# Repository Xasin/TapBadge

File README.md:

# TapBadge
DIY Smart Home touch badge - control things like in StarTrek!

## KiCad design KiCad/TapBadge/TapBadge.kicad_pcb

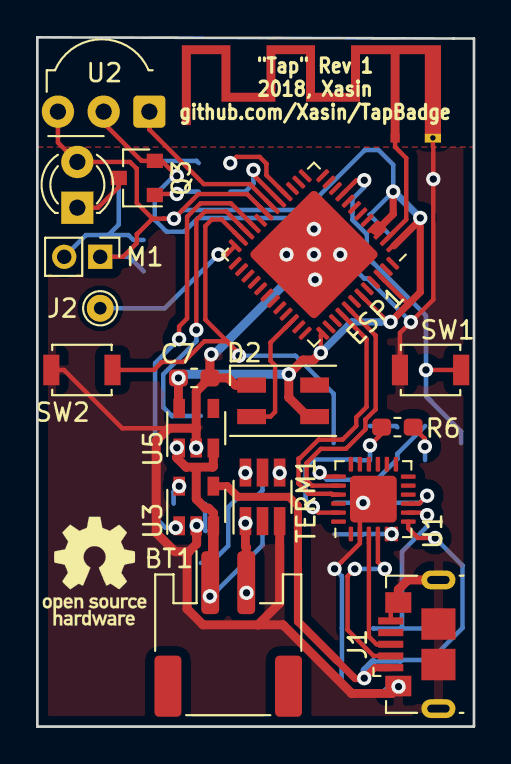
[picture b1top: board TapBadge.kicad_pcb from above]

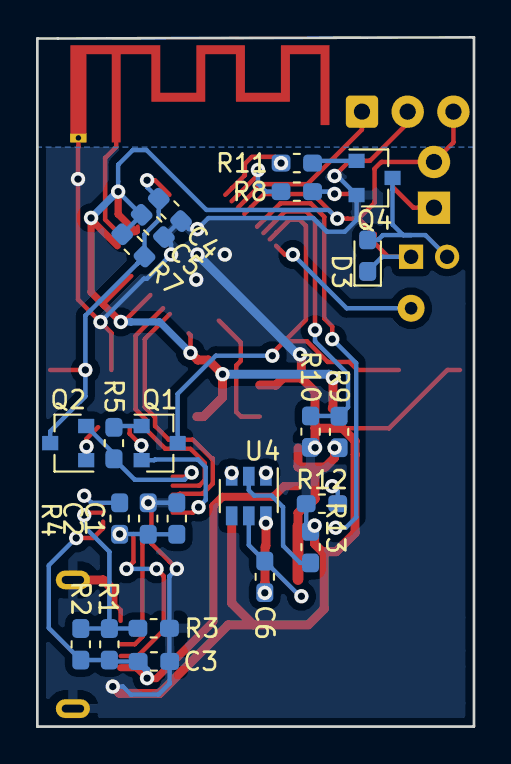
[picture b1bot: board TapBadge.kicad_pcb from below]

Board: 2 copper layers, 24.3 x 38.3 mm, 41 parts (23 on the bottom side), 34 nets.

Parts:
AE1: Antenna_Dipole; Texas_SWRA117D_2.4GHz_Left
BT1: Battery_Cell; JST_PH_S2B-PH-SM4-TB_1x02-1MP_P2.00mm_Horizontal
C1, C3, C7: 10uF; C_0603_1608Metric_Pad1.05x0.95mm_HandSolder
C2, C4, C5, C6: 100nF; C_0603_1608Metric_Pad1.05x0.95mm_HandSolder
D1: SFH4346; LED_D3.0mm_IRBlack
D2: WS2812B; LED_SK6812MINI_PLCC4_3.5x3.5mm_P1.75mm
D3: D_Schottky; D_0603_1608Metric_Pad1.05x0.95mm_HandSolder
ESP1: ESP32PICO_D4; QFN-48-1EP_7x7mm_P0.5mm_EP5.15x5.15mm
J1: USB_B_Mini; USB_Micro-B_GCT_USB3076-30-A
J2: Conn_01x01_Male; TestPoint_THTPad_D1.5mm_Drill0.7mm
M1: Motor_DC_ALT; PinHeader_1x02_P2.00mm_Vertical
Q1, Q2, Q3, Q4: Q_NPN_BEC; SOT-23
R1: R_Small; R_0603_1608Metric_Pad1.05x0.95mm_HandSolder
R2, R3, R5, R6, R7, R11: 10k; R_0603_1608Metric_Pad1.05x0.95mm_HandSolder
R4, R8, R12, R13: 2.2k; R_0603_1608Metric_Pad1.05x0.95mm_HandSolder
R9, R10: 100k; R_0603_1608Metric_Pad1.05x0.95mm_HandSolder
SW1, SW2: SW_Push; SW_SPST_B3U-1000P
TERM1: FS8205; SOT-23-6_Handsoldering
U1: CP2102N-A01-GQFN24; QFN-24-1EP_4x4mm_P0.5mm_EP2.6x2.6mm
U2: TSOP4840; Vishay_MOLD-3Pin
U3: MCP73831-2-OT; SOT-23-5
U4: FS312F-G; SOT-23-6
U5: SPX3819M5-L-3-3; SOT-23-5

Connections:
+3V3: C5.1, C7.1, D1.2, D2.1, D3.1, ESP1.1, ESP1.3, ESP1.4, ESP1.19, ESP1.37, ESP1.43, ESP1.46, M1.1, R7.1, U2.3, U5.5
+5V: C3.2, J1.1, R1.1, R2.1, U1.7, U3.4
+BATT: BT1.1, C6.2, R9.1, U3.3, U4.5, U5.1, U5.3
/ANT: AE1.1, ESP1.2
/CHG_STAT: ESP1.21, U3.1
/E->U: ESP1.41, U1.20
/GPIO0: ESP1.23, Q1.3, SW2.2
/IR_IN: ESP1.18, U2.1
/IR_OUT: ESP1.17, R8.2
/RESET: C4.1, ESP1.9, Q2.3, R7.2, SW1.2
/RGB_IO: D2.4, ESP1.34
/TOUCH0: ESP1.24, J2.1
/U->E: ESP1.40, U1.21
/VBR: ESP1.16, R11.2
GND: AE1.2, C1.2, C2.2, C3.1, C4.2, C5.2, C7.2, D2.3, ESP1.49, J1.5, J1.6, Q3.2, Q4.2, R3.2, R10.2, R12.1, R13.2, SW1.1, SW2.1, TERM1.3, U1.2, U1.25, U2.2, U3.2, U5.2
unnamed: BT1.2, C6.1, TERM1.1, U4.6
unnamed: C1.1, C2.1, R4.1, U1.5, U1.6
unnamed: D1.1, Q3.3
unnamed: D3.2, M1.2, Q4.3
unnamed: ESP1.22, R9.2, R10.1
unnamed: J1.2, U1.4
unnamed: J1.3, U1.3
unnamed: Q1.1, R5.1
unnamed: Q1.2, R6.2, U1.23
unnamed: Q2.1, R6.1
unnamed: Q2.2, R5.2, U1.19
unnamed: Q3.1, R8.1
unnamed: Q4.1, R11.1
unnamed: R1.2, R2.2, R3.1, U1.8
unnamed: R4.2, U1.9
unnamed: R12.2, U3.5
unnamed: R13.1, U4.2
unnamed: TERM1.4, U4.3
unnamed: TERM1.6, U4.1

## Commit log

2018-09-01 ESP32 build env init
2018-09-10 First playing around with ESP
2018-09-10 First rev of the Tap Badge schematic. WIP
2018-09-16 Using C++, added Touch and NeoPixel classes
2018-09-16 Completed rev1 PCB
2018-10-08 Added last few 3D models
2018-10-08 Small timer type change
2018-10-08 Fixed mutex usage
2018-10-08 Updated config for BT
2018-10-08 Added handler for LED output
2018-10-08 First version of a BLE handler class
2018-10-08 Included new BLE class
2018-10-14 BLE Service file added
2018-10-14 BLE Characteristic class added
2018-10-14 Using new classes in handler
2018-10-14 Testing classes
2018-10-14 SDKConfig update
2018-10-17 Got the BLEHandler system into a working state
2018-10-19 Tried fixing bluetooth characteristic update fail
2018-10-20 Removed charge status pin
2018-10-20 Added read and write functions to Characteristic.h
2018-10-20 Playing with stuff
2018-10-23 Added 'return to base color' function
2018-10-23 Small improvements to NeoController
2018-10-23 Added ISR triggering and detect handle notifying
2018-10-23 Rev.1 of the morsecode parser :D
2018-10-23 Trying to power-optimize BLE
2018-10-23 Playing with BLE power
2018-10-23 Added better mode control
2018-10-23 Added 'off' command
2018-10-24 Small mods to Main
2018-10-24 Moved bluedroid init into contstructor
2018-10-24 Stripping project to minimal error production
2018-10-24 Debug work
2018-10-24 Removed encryption
2018-10-24 Added status target for powerdown phase
2018-10-24 Added convenience value setter functions
2018-10-24 Made Services default primary
2018-10-24 Added pre-built components
2018-10-24 Played with new components
2018-10-25 Added power-target for auto-power-down
2018-10-25 Forgot to add main
2018-10-26 Attempt at debouncing
2018-10-31 Fine tuning of values
2018-10-31 Fixed CPU freq to 80MHz
2018-10-31 Fixed adv-stop with no stop time
2018-10-31 First small version of the TapApp
2018-10-31 Added gitignore for the build output
2018-11-05 Added client connection timestamp and fixed data send
2018-11-05 Changed threshold value
2018-11-05 Added cyclical reconnecting
2018-11-05 First, cleaner version of the auto-reconnect-system
2018-11-05 Used the new BLE code
2018-11-05 Lots of background random changes, I suppose
2018-11-05 Removed .pro.user file due to version problems
2018-11-06 Added enum to Qt, added timerUpdated emitters
2018-11-06 Added handler-getter
2018-11-06 Exposed classes and used new functions
2018-11-06 Working on a fancy UI now
2018-11-07 Began working on the countdown bar
2018-11-07 Finally got the .pro.user files under control >:C
2018-11-07 Made the 'find' function QML-Callable
2018-11-07 Added Q_PROPERTIES for battery voltage, percent, whoIs
2018-11-07 Used fancy new stuff
2018-11-07 Made whoIs readable
2018-11-07 SDKconfig changes...?
2018-11-07 Merged
2018-11-08 Working on a background-running app
2018-11-08 Removed QtApplicationmanager dependency
2018-11-08 Visual improvements
2018-11-15 Added MQTT connetion to TapApp
2018-11-15 Added data clear function
2018-11-15 Added read-callback
2018-11-15 Added mqtt module
2018-11-15 Threshold adjustment
2018-11-15 Added readout callback
2018-11-17 Reduced connection time to 10s, changed some colors
2018-11-19 Working on new, SPP based BT code
2018-11-20 Working on Base64 packet decode
2018-11-22 Added connected-metric, data decoding, working on SPP Values
2018-11-22 Removed debug & added safeguards
2018-11-22 Rewrote & added Value-related functions
2018-11-22 Tested new value functions
2018-11-24 Tried to get template functions working - nope
2018-11-26 Found out how to template
2018-11-26 Started working on Qt-Side SPP code
2018-11-27 Trying to get SPP connection to work
2018-11-28 Fixed SPP connect, thanks Mesh
2018-11-28 Added proper value class
2018-11-28 Tested new values
2018-11-29 Started reworking to SPP code
2018-12-01 Managed to get battery stat working
2018-12-01 Tried adding disable/enable. BUGS OUT
2018-12-01 Tried using new disable/enable
2018-12-02 Reenabled MEM release
2018-12-02 Disabled SPP disabling (so it stops crashing)
2018-12-02 Tried to get Qt background service to work. Egh
2018-12-02 SDK update
2018-12-06 Began working on the Java file for the service
2018-12-07 Began integrating the Java service file
2019-01-13 Small adjustments, gonna work in the new register coms soon
2019-01-14 Added ESP32 XasCode libraries
2019-01-14 Once used KiCAD 5 >.>
2019-01-14 Fiddled with lotsa Tap code, moving to BLE now
2019-01-14 Small Tap changes?
2019-01-15 Moer fiddles with Qt
2019-01-16 Began testing new BLE code
2019-01-16 Began implementing the new BLE code
2019-01-17 Began fine-tuning MQTT and BT
2019-02-01 Tweaked a few connection settings
2019-02-01 Small tweaks regarding reconnection
2019-02-04 Playing with MQTT code
2019-02-08 Tested new MQTT Registers
2019-03-15 Added debug output
2019-03-15 Adjusted our colors somewhat, used MQTT's Wifi Convenience
2019-03-15 Removed local Touch sensing class
